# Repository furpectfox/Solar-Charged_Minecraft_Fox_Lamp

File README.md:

# Solar-Charged Minecraft Fox Lamp
***Description***: This sleep lamp is powered by two Ni-Cd cells wired in series for a total of 2.4V and can be charged using a small solar panel. The Red and Green LEDs of an RGB LED are used to produce the orange light, consuming ~30mA combined.

***Charging***: A transistor-based constant current circuit trickle-charges the two Ni-Cd cells at 60mA using a 9V solar panel.

***Usage***: The lamp provides approximately 16 hours of usable light on a full charge.

## [Schematic](schematic.pdf)

## PCB
***[PCB was etched at home using a PCB Pen Plotter attachment](https://github.com/furpectfox/PCB_Trace_Plotter)**  

## Finish

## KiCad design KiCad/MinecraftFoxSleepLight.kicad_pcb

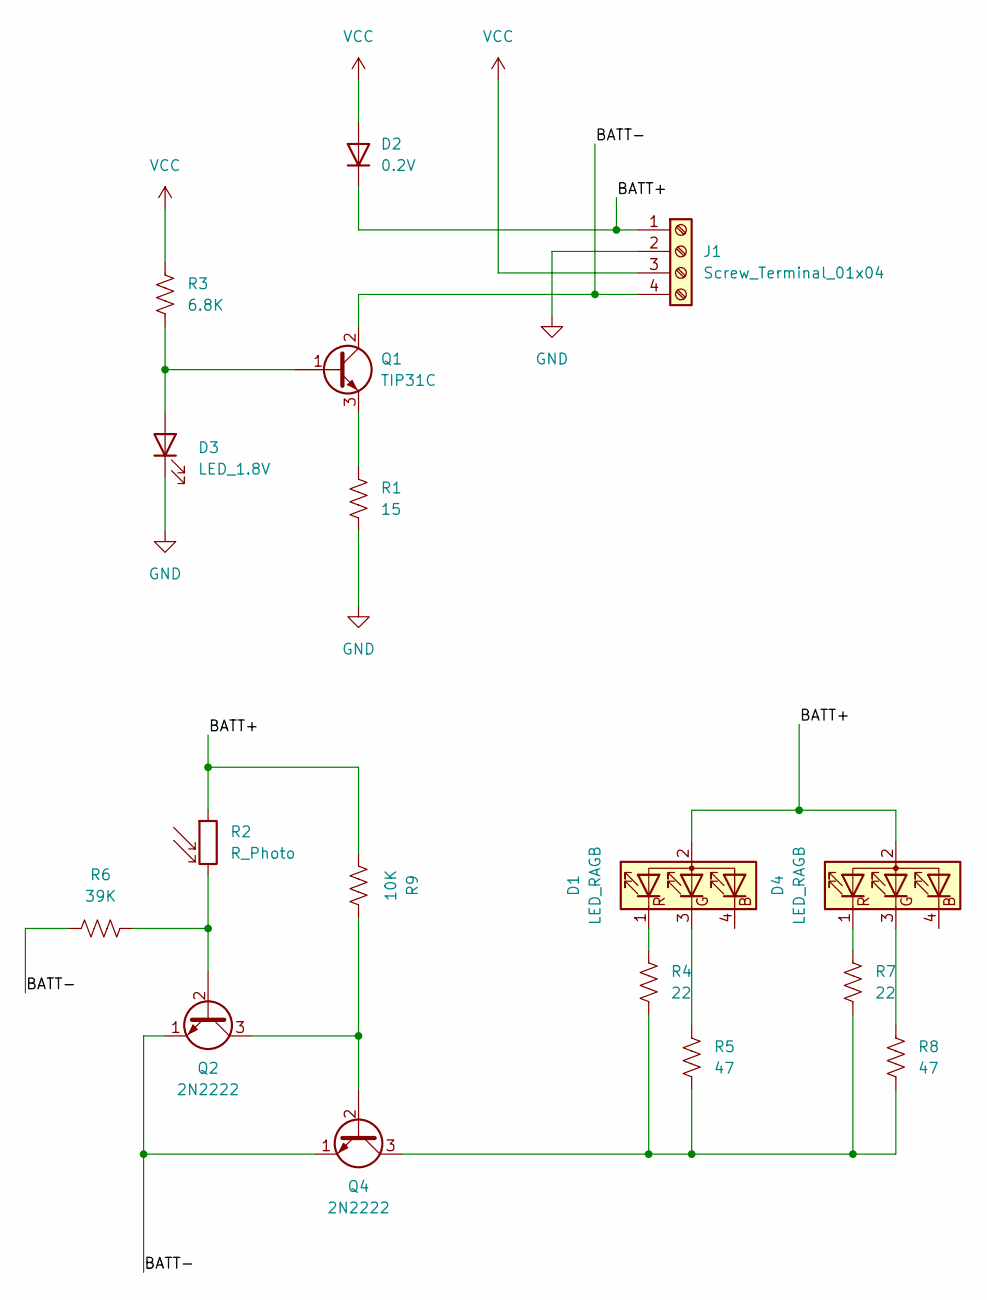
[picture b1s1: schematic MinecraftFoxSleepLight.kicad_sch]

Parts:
D1, D4: LED_RAGB; PinHeader_1x04_P2.54mm_Vertical
D2: 0.2V; D_A-405_P7.62mm_Horizontal
D3: LED_1.8V; LED_D3.0mm_Horizontal_O3.81mm_Z2.0mm
J1: Screw_Terminal_01x04; TerminalBlock_Altech_AK300-4_P5.00mm
Q1: TIP31C; TO-220-3_Horizontal_TabDown
Q2, Q4: 2N2222; TO-92_Inline_Wide
R1: 15; R_Axial_DIN0207_L6.3mm_D2.5mm_P7.62mm_Horizontal
R2: R_Photo; R_LDR_5.0x4.1mm_P3mm_Vertical
R3: 6.8K; R_Axial_DIN0207_L6.3mm_D2.5mm_P7.62mm_Horizontal
R4, R7: 22; R_Axial_DIN0207_L6.3mm_D2.5mm_P7.62mm_Horizontal
R5, R8: 47; R_Axial_DIN0207_L6.3mm_D2.5mm_P7.62mm_Horizontal
R6: 39K; R_Axial_DIN0207_L6.3mm_D2.5mm_P7.62mm_Horizontal
R9: 10K; R_Axial_DIN0207_L6.3mm_D2.5mm_P7.62mm_Horizontal

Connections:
/BATT+: D1.2 (A), D2.1 (K), D4.2 (A), J1.1, R2.1, R9.1
/BATT-: J1.4, Q1.2 (C), Q2.1 (E), Q4.1 (E), R6.1
GND: D3.1 (K), J1.2, R1.2
unnamed: D1.3 (GK), R5.1
unnamed: D1.1 (RK), R4.1
unnamed: D3.2 (A), Q1.1 (B), R3.2
unnamed: D4.3 (GK), R8.1
unnamed: D4.1 (RK), R7.1
unnamed: Q1.3 (E), R1.1
unnamed: Q2.2 (B), R2.2, R6.2
unnamed: Q2.3 (C), Q4.2 (B), R9.2
unnamed: Q4.3 (C), R4.2, R5.2, R7.2, R8.2
VCC: D2.2 (A), J1.3, R3.1

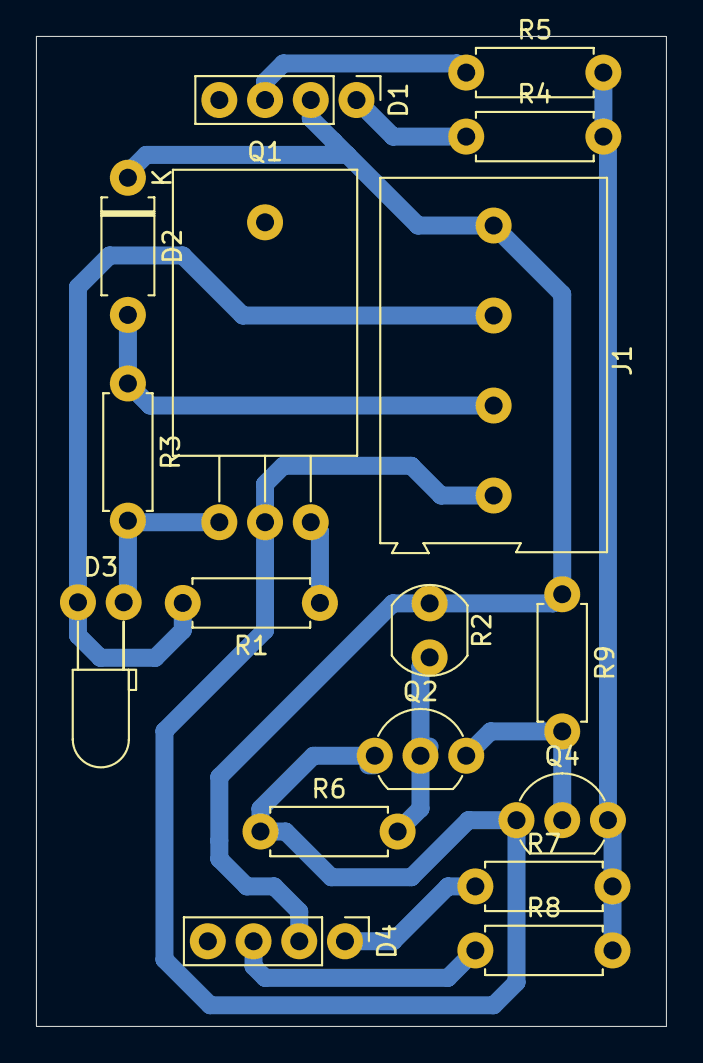
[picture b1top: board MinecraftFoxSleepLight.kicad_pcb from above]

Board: 2 copper layers, 35.0 x 55.0 mm, 17 parts (0 on the bottom side), 13 nets.

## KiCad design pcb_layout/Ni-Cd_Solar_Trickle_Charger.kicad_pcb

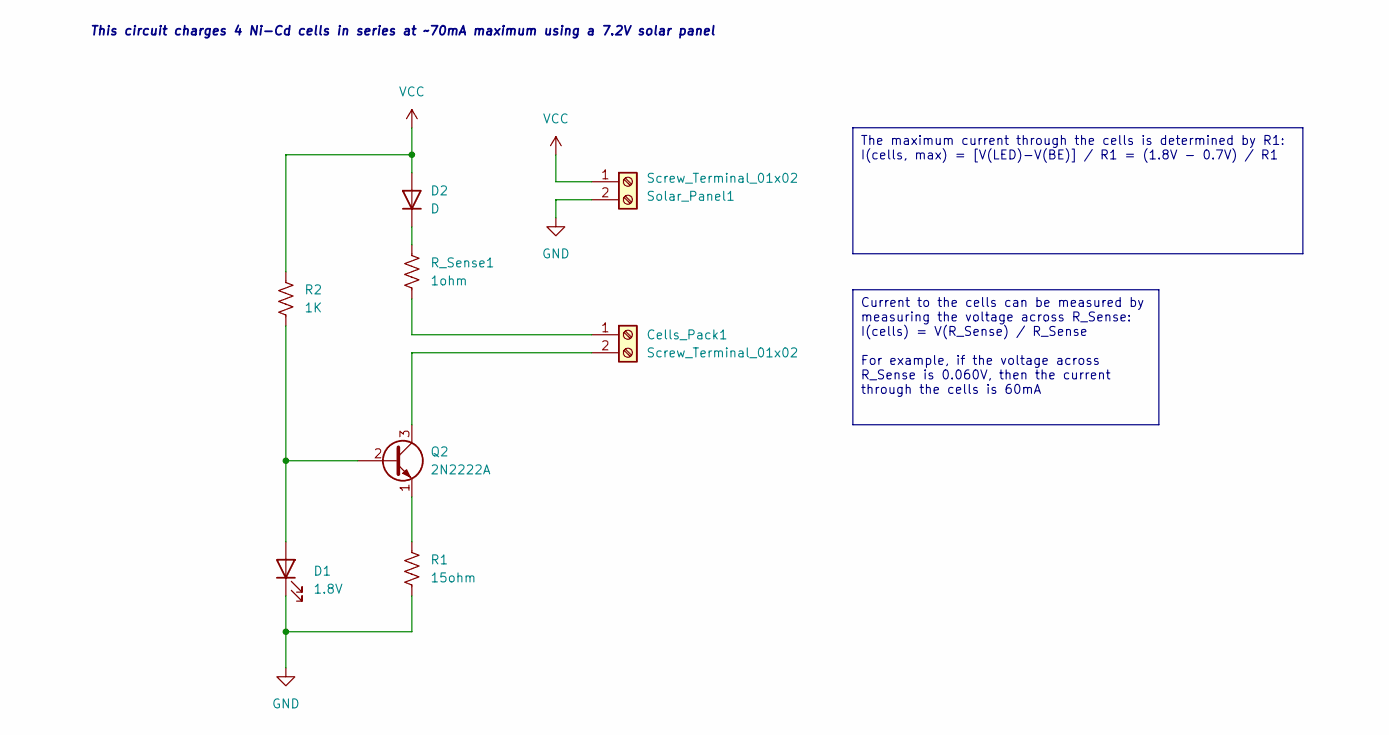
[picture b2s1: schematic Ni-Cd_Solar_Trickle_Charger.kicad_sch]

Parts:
Cells_Pack1: Screw_Terminal_01x02; TerminalBlock_Altech_AK300-2_P5.00mm
D1: 1.8V; LED_D5.0mm
D2: D; D_A-405_P7.62mm_Horizontal
Q2: 2N2222A; TO-92L_Inline_Wide
R1: 15ohm; R_Axial_DIN0207_L6.3mm_D2.5mm_P7.62mm_Horizontal
R2: 1K; R_Axial_DIN0207_L6.3mm_D2.5mm_P7.62mm_Horizontal
R_Sense1: 1ohm; R_Axial_DIN0207_L6.3mm_D2.5mm_P7.62mm_Horizontal
Solar_Panel1: Screw_Terminal_01x02; TerminalBlock_Altech_AK300-2_P5.00mm

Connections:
GND: D1.1 (K), R1.2, Solar_Panel1.2
unnamed: Cells_Pack1.1, R_Sense1.2
unnamed: Cells_Pack1.2, Q2.3 (C)
unnamed: D1.2 (A), Q2.2 (B), R2.2
unnamed: D2.1 (K), R_Sense1.1
unnamed: Q2.1 (E), R1.1
VCC: D2.2 (A), R2.1, Solar_Panel1.1

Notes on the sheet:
The maximum current through the cells is determined by R1: I(cells, max) = [V(LED)-V(BE)] / R1 = (1.8V - 0.7V) / R1
Current to the cells can be measured by measuring the voltage across R_Sense: I(cells) = V(R_Sense) / R_Sense For example, if the voltage across R_Sense is 0.060V, then the current through the cells is 60mA
This circuit charges 4 Ni-Cd cells in series at ~70mA maximum using a 7.2V solar panel

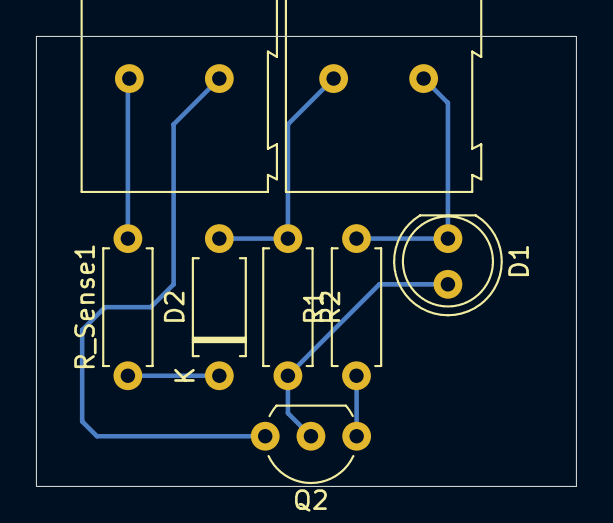
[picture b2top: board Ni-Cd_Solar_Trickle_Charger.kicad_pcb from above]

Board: 2 copper layers, 30.0 x 25.0 mm, 8 parts (0 on the bottom side), 7 nets.

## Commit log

2024-07-24 add schematic and pcb layout
2025-03-03 update schematic
2025-03-09 add KiCad folder
2025-03-09 add file to KiCad folder
